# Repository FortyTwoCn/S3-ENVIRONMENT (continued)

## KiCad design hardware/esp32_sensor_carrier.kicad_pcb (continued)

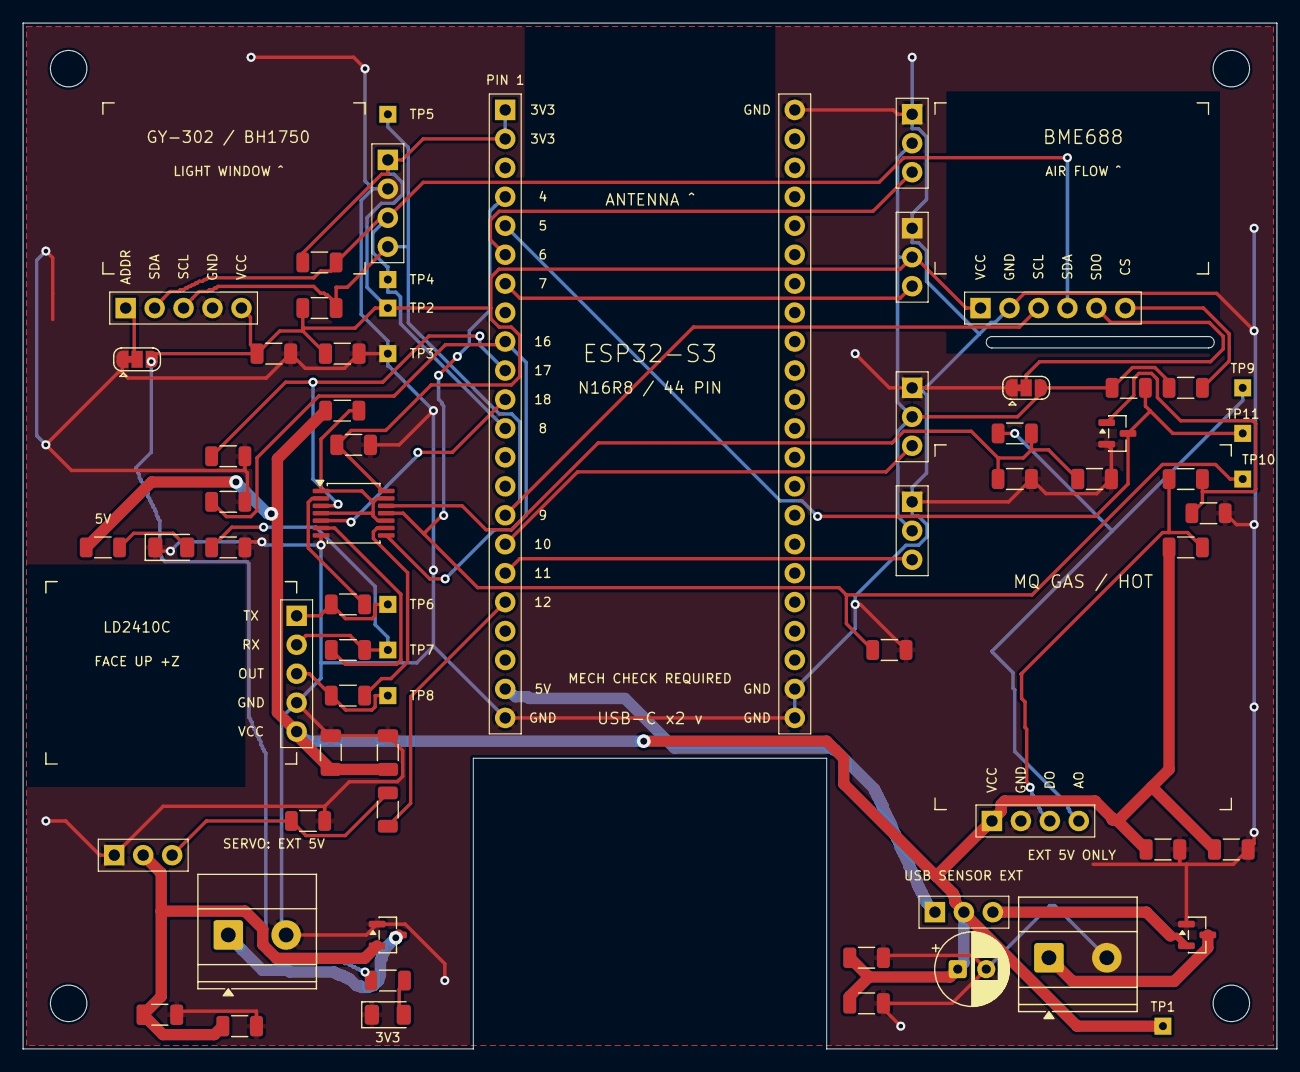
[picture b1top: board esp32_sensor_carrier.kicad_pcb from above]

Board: 2 copper layers, 110.0 x 90.0 mm, 71 parts (0 on the bottom side), 37 nets.

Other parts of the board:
H1, H2, H3, H4: MountingHole_3.2mm_M3

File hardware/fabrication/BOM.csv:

References,Value / Part,Quantity,Footprint,Population,Notes
J1,1x22 Female Header,2,ESP32-S3_N16R8_44PIN_CARRIER,FIT,2.54mm pitch; straight through-hole; >=8.5mm body height; 25.40mm row spacing
J2,1x5 Female Header,1,GY-302_BH1750_SOCKET,FIT,GY-302; 2.54mm pitch; >=8.5mm height
J3,1x6 Female Header,1,BME688_SOCKET,FIT,BME688; 2.54mm pitch; >=8.5mm height
J4,1x5 Female Header,1,LD2410C_SOCKET,FIT,LD2410C; 2.54mm pitch; >=8.5mm height
J5,1x4 Female Header,1,MQ_GAS_SOCKET,FIT,MQ; 2.54mm pitch; >=8.5mm height
JP1,3-pad copper solder selector,0,SolderJumper-3_P1.3mm_Bridged12_RoundedPad1.0x1.5mm,PCB FEATURE,Factory copper bridge 1-2=GND; cut before soldering 2-3=3V3
JP2,3-pad copper solder selector,0,SolderJumper-3_P1.3mm_Bridged12_RoundedPad1.0x1.5mm,PCB FEATURE,Factory copper bridge 1-2=GND; cut before soldering 2-3=3V3
"R1, R8, R21, R20",10k,4,R_1206_3216Metric,FIT,"1206, 1%, 0.25 W"
"R2, R3",4.7k DNP,2,R_1206_3216Metric,DNP,"1206, 1%, 0.25 W"
R4,6.8k,1,R_1206_3216Metric,FIT,"1206, 1%, 0.25 W"
R5,7.5k,1,R_1206_3216Metric,FIT,"1206, 1%, 0.25 W"
"C1, C2, C5, C7, C9, C11, C13",100nF,7,C_1206_3216Metric,FIT,1206 X7R; 10uF >=16V; 100nF >=25V
R6,33k,1,R_1206_3216Metric,FIT,"1206, 1%, 0.25 W"
"R7, R12, R13, R14, R15, R19",100k,6,R_1206_3216Metric,FIT,"1206, 1%, 0.25 W"
Q1,AO3400A,1,SOT-23,FIT,N-MOS inverter; 1=G 2=S 3=D; insulated gate prevents 5V signal back-power when 3V3 is off
U1,TMUX1511PWR,1,TSSOP-14_4.4x5mm_P0.65mm,FIT,"Four powered-off protected SPST switches; SEL tied to SENSOR_5V, fail-safe 5.5V controls"
"R9, R10, R11, R18",1k,4,R_1206_3216Metric,FIT,"1206, 1%, 0.25 W"
"J6, J13",2-pin 5.08mm screw terminal,2,"TerminalBlock_Phoenix_MKDS-1,5-2-5.08_1x02_P5.08mm_Horizontal",FIT,5V ONLY; pin1 positive pin2 GND; input wire clearance required
Q2,AO3401A,1,SOT-23,FIT,"P-MOS reverse polarity protection, source on protected output; body diode raw -> protected"
JP3,1x3 Male Header,1,POWER_SELECT_1x03,FIT,2.54mm pitch; selector; one rated >=3A shunt only
C3,100uF 16V,1,CP_Radial_D6.3mm_P2.50mm,FIT,"Low ESR polarized electrolytic, 6.3mm diameter, 2.5mm pitch"
"C4, C6, C8, C10, C12",10uF,5,C_1206_3216Metric,FIT,1206 X7R; 10uF >=16V; 100nF >=25V
"R16, R17",2.2k,2,R_1206_3216Metric,FIT,"1206, 1%, 0.25 W"
D1,GREEN,1,LED_1206_3216Metric,FIT,
D2,AMBER,1,LED_1206_3216Metric,FIT,
J7,1x4 Male Header,1,EXT_I2C_1x04,FIT,2.54mm pitch; EXT_I2C 3V3/GND/SDA/SCL
J8,1x3 Male Header,1,GPIO_1x03,FIT,GPIO6; 2.54mm pitch; see interface pinout
J9,1x3 Male Header,1,GPIO_1x03,FIT,GPIO7; 2.54mm pitch; see interface pinout
J10,1x3 Male Header,1,GPIO_1x03,FIT,GPIO10; 2.54mm pitch; see interface pinout
J11,1x3 Male Header,1,GPIO_1x03,FIT,GPIO11; 2.54mm pitch; see interface pinout
J12,1x3 Male Header,1,SERVO_1x03,FIT,SERVO; 2.54mm pitch; see interface pinout
Q3,AO3401A,1,SOT-23,FIT,Independent servo rail reverse polarity protection
JP3-SHUNT,2.54mm jumper cap,1,Accessory,FIT,>=3A rated; default 2-3 EXT; never bridge all three pins
TP1-TP11,Plated test pads,0,1.5mm pad / 0.7mm drill,PCB FEATURE,Optional test hooks or solder pins; no fitted part required
H1-H4,M3 mounting hardware,4,3.2mm NPTH,OPTIONAL,Nylon standoffs recommended; no metal above antenna regions
MODULE-ESP,ESP32-S3 N16R8 44-pin board,1,USER PROVIDED MODULE,USER INSTALLED,Dual Type-C CH343P board matching supplied photo; do not place in PCB SMT order
MODULE-GY,GY-302 / BH1750 module,1,USER PROVIDED MODULE,USER INSTALLED,Sensing face up: ADDR/SDA/SCL/GND/VCC from carrier pin1; verify straight downward header
MODULE-BME,BME688 I2C module,1,USER PROVIDED MODULE,USER INSTALLED,VCC/GND/SCL/SDA/SDO/CS must match actual module
MODULE-LD,HLK-LD2410C module,1,USER PROVIDED MODULE,USER INSTALLED,TX/RX/OUT/GND/VCC; 3.3V logic
MODULE-MQ,MQ gas module,1,USER PROVIDED MODULE,USER INSTALLED,Sensing face up: VCC/GND/DO/AO from carrier pin1; 5V heater; right-angle header needs replacement for horizontal mounting

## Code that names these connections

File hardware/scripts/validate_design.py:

"""Independent manifest/netlist/PCB checks, plus bounded input-voltage calculations."""
import pathlib,json,csv,xml.etree.ElementTree as ET,itertools,hashlib
from shapely.geometry import box,LineString,Point
R=pathlib.Path(__file__).resolve().parents[1]
read=lambda f:json.loads((R/f).read_text(encoding='utf-8'))
M=read('fabrication/design_manifest.json'); G=read('checks/geometry.json')
xml=ET.parse(R/'fabrication/netlist.xml'); nets={}
for net in xml.findall('./nets/net'):
 for node in net.findall('node'):nets[(node.get('ref'),node.get('pin'))]=net.get('name')
actual={(g['ref'],g['pin']):g['net'] for g in G if g['kind']=='pad' and g['ref'].startswith(('J','R','C','U','Q','D','TP'))}
results=[]
def check(name,ok,detail):
 results.append({'check':name,'status':'PASS' if ok else 'FAIL','detail':detail})
 if not ok:raise AssertionError(name+': '+str(detail))
expected={(c['ref'],p['number']):p['net'] for c in M['components'] for p in c['pins'] if p['net']}
check('manifest_netlist_pcb_pad_parity',all(nets[k]==n and actual[k]==n for k,n in expected.items()),f'{len(expected)} assigned pins checked against KiCad XML and physical PCB pads')
def pins(ref,ns):check(ref+'_pinout',all(actual[(ref,str(i+1))]==n for i,n in enumerate(ns)),ns)
pins('J2',['BH_ADDR','I2C_SDA','I2C_SCL','GND','+3V3'])
pins('J3',['+3V3','GND','I2C_SCL','I2C_SDA','BME_ADDR','BME_CS'])
pins('J4',['RADAR_TX','RADAR_RX','RADAR_OUT','GND','SENSOR_5V'])
pins('J5',['SENSOR_5V','GND','MQ_DO_RAW','MQ_AO_RAW'])
pins('JP3',['ESP32_5V','SENSOR_5V','EXT_5V'])
pins('Q1',['MQ_BASE','GND','MQ_DO_3V3']);pins('Q2',['GND','EXT_5V','EXT_5V_RAW']);pins('Q3',['GND','5V_SERVO','SERVO_5V_RAW'])
pins('U1',['SENSOR_ENABLE','RADAR_TX_LIMIT','RADAR_TX_ESP','SENSOR_ENABLE','RADAR_RX_ESP','RADAR_RX_SWITCH','GND','RADAR_OUT_ESP','RADAR_OUT_LIMIT','SENSOR_ENABLE','MQ_ADC','MQ_ADC_FILTER','SENSOR_ENABLE','+3V3'])
for ref,ns in {'R4':['MQ_AO_RAW','MQ_ADC_FILTER'],'R5':['MQ_ADC_FILTER','GND'],'C1':['MQ_ADC_FILTER','GND'],'R9':['RADAR_TX','RADAR_TX_LIMIT'],'R10':['RADAR_RX_SWITCH','RADAR_RX'],'R11':['RADAR_OUT','RADAR_OUT_LIMIT'],'R8':['+3V3','MQ_DO_3V3'],'R15':['MQ_ADC','GND']}.items():pins(ref,ns)
gpio={'4':'MQ_ADC','5':'MQ_DO_3V3','8':'I2C_SDA','9':'I2C_SCL','16':'RADAR_OUT_ESP','17':'RADAR_TX_ESP','18':'RADAR_RX_ESP','6':'GPIO6','7':'GPIO7','10':'GPIO10','11':'GPIO11','12':'SERVO_PWM'}
j1=next(c for c in M['components'] if c['ref']=='J1')
check('GPIO_photo_pin_order',all(actual[('J1',p['number'])]==gpio[p['name']] for p in j1['pins'] if p['name'] in gpio),gpio)
check('reserved_pins_NC',all(not p['net'] for p in j1['pins'] if p['name'] in ['19','20','35','36','37','0','3','45','46','48']), 'USB, PSRAM, strapping, RGB pins unused by carrier')
check('no_5V_net_on_GPIO',all(p['net'] not in ['SENSOR_5V','ESP32_5V','EXT_5V','MQ_AO_RAW','MQ_DO_RAW','5V_SERVO'] for p in j1['pins'] if p['name'] not in ['5V','3V3','GND']), 'GPIO inputs have defined low-voltage networks')
for k2,rail in [('ESP32','ESP32_5V'),('SENSOR','SENSOR_5V'),('EXT','EXT_5V')]:
 check('selector_'+k2,actual[('JP3',str(['ESP32','SENSOR','EXT'].index(k2)+1))]==rail,'No copper bridge between three independently named rails; one removable shunt selected by user')
pins('J12',['GND','5V_SERVO','SERVO_SIGNAL']);pins('J13',['SERVO_5V_RAW','GND'])
rbot=lambda r5,r15:1/(1/r5+1/r15)
gain=lambda rt,r5,r15:rbot(r5,r15)/(rt+rbot(r5,r15))
nom=gain(6800,7500,100000);worst=5.25*gain(6800*.99,7500*1.01,100000*1.01)
check('MQ_ADC_max_5V25_1pct',worst<2.9,{'nominal_ratio':nom,'at_5V':5*nom,'maximum_V':worst,'limits':'regulated 5V +/-5%; all resistors 1%; includes R15 loading; U1 Ron <=4.5 ohm only reduces this bound'})
gate=4.75*100000*.99/(100000*.99+33000*1.01+10000*1.01)
check('MQ_DO_open_collector_gate',gate>2.5,{'minimum_high_V':gate,'note':'includes fitted R21 10k, R6 33k, R7 100k; AO3400A specified at Vgs=2.5V'})
check('powered_off_leak_bound',2e-6*101000<.3,{'GPIO_off_max_V':2e-6*101000,'condition':'TMUX1511 max powered-off leakage 2uA/channel; 100k 1% pulldown; protected inputs <=3.6V'})
components=[]
for (a,aa),(b,bb) in itertools.combinations(M['envelopes'].items(),2):
 pa,pb=box(*aa),box(*bb);check('envelope_'+a+'_'+b,not pa.intersects(pb),{'separation_mm':round(pa.distance(pb),3),'status':'provisional module envelopes; actual headers/body offsets require physical verification'})
for name,bounds in M['keepouts'].items():
 forbidden=box(*bounds).buffer(-.001);hits=[]
 for g in G:
  if g['kind']=='track':shape=LineString([g['start'],g['end']]).buffer(g['width']/2)
  elif g['kind']=='via':shape=Point(g['center']).buffer(g['width']/2)
  else:shape=box(*g['box'])
  if shape.intersects(forbidden):hits.append(g['id'])
 check(name+'_trace_via_pad_keepout',not hits,{'bounds_mm':bounds,'hits':hits,'copper_fill':'KiCad keepout rule plus zero DRC; Gerber viewer visual check separately'})
tracks=[g for g in G if g['kind']=='track'];vias=[g for g in G if g['kind']=='via']
check('signal_track_width',min(g['width'] for g in tracks)>=.25,{'min_width_mm':min(g['width'] for g in tracks)})
power={n:round(min(g['width'] for g in tracks if g['net']==n),3) for n in ['SENSOR_5V','ESP32_5V','EXT_5V','EXT_5V_RAW','5V_SERVO','SERVO_5V_RAW']}
necks=[g for g in tracks if g['net']=='EXT_5V' and g['width']<1]
neck_len=sum(LineString([g['start'],g['end']]).length for g in necks)
check('power_track_width',all(v>=1 for n,v in power.items() if n!='EXT_5V') and power['EXT_5V']>=.6 and neck_len<2.5 and all(box(100,79,104,82).covers(LineString([g['start'],g['end']])) for g in necks),{'minimum_width_mm':power,'Q2_short_pad_escape_length_mm':round(neck_len,3),'note':'0.601 mm escape only at SOT-23 source pad; 1.0 mm main rails and MQ branch'})
check('four_M3_NPTH',len([g for g in G if g['kind']=='pad' and g['ref'].startswith('H')])==4,'4 x 3.2 mm NPTH at (4,4), (106,4), (4,86), (106,86); drill file separately checked')
drc=read('checks/drc_final.json');erc=read('checks/erc.json')
project=read('esp32_sensor_carrier.kicad_pro')
rules=project['board']['design_settings']
check('DRC_all_rules_active',not rules.get('drc_exclusions') and not any(v=='ignore' for v in rules['rule_severities'].values()),'All listed DRC rules use error/warning; no disabled categories or exclusions')
check('DRC_no_exclusions',not drc['violations'] and not drc['unconnected_items'] and not drc['schematic_parity'],{'violations':len(drc['violations']),'unconnected':len(drc['unconnected_items']),'parity':len(drc['schematic_parity'])})
check('ERC',not any(s['violations'] for s in erc['sheets']), 'No error/warning exclusions used; NC and power flags explicit')
results.append({'check':'actual_module_mechanics','status':'PENDING','detail':'Header spacing/pitch and ESP external size from supplied dimensioned photo. ESP end offsets, module pin orientations/body envelopes/USB plugs require physical check. Not production verified.'})
out={'status':'ELECTRICAL_AND_ROUTING_PASS_MECHANICAL_PENDING','checks':results,'calculated_MQ_ADC_ratio':nom,'calculated_MQ_ADC_max_V':worst,'track_count':len(tracks),'via_count':len(vias),'hardware_tested':False}
(R/'checks/design_validation.json').write_text(json.dumps(out,ensure_ascii=False,indent=2)+'\n',encoding='utf-8')
print(f'{len(results)-1} automatic checks PASS; mechanical verification PENDING; ADC max {worst:.4f} V')
